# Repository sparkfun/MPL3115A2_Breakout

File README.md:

SparkFun MPL3115A2 Altitude/Pressure Sensor Breakout
====================================================

[  
*MPL3115A2 Altitude/Pressure Sensor Breakout (SEN-11084)*](https://www.sparkfun.com/products/11084)

The MPL3115A2 is a MEMS pressure sensor that provides Altitude data to within 30cm (with oversampling enabled). The sensor outputs are digitized by a high resolution 24-bit ADC and transmitted over I2C, meaning it's easy to interface with most controllers.

Repository Contents
-------------------
* **/Firmware** - Example Arduino sketch to use with the sensor.
* **/Hardware** - All Eagle design files (.brd, .sch)
* **/Libraries** - All Arduino libraries

Documentation
--------------
* **[Library](https://github.com/sparkfun/SparkFun_MPL3115A2_Breakout_Arduino_Library)** - Arduino library for the MPL3115A2.
* **[Hookup Guide](https://learn.sparkfun.com/tutorials/mpl3115a2-pressure-sensor-hookup-guide)** - Basic hookup guide for the MPL3115A2 Breakout.
* **[SparkFun Fritzing repo](https://github.com/sparkfun/Fritzing_Parts)** - Fritzing diagrams for SparkFun products.
* **[SparkFun 3D Model repo](https://github.com/sparkfun/3D_Models)** - 3D models of SparkFun products. 

License Information
-------------------
The hardware is released under [Creative Commons ShareAlike 4.0 International](https://creativecommons.org/licenses/by-sa/4.0/).
The code is beerware; if you see me (or any other SparkFun employee) at the local, and you've found our code helpful, please buy us a round!

Distributed as-is; no warranty is given.

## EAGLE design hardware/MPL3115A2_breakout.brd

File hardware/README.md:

# What Are these Files?

The .sch and .brd files hare are Eagle CAD schematic and PCB design files for the MPL3115A2 Breakout.

These files were created with Eagle 6.2.0. There is a free, lite, version of Eagle available from [cadsoftusa.com](cadsoftusa.com).

[Creative Commons Attribution-ShareAlike](http://creativecommons.org/licenses/by-sa/3.0/)

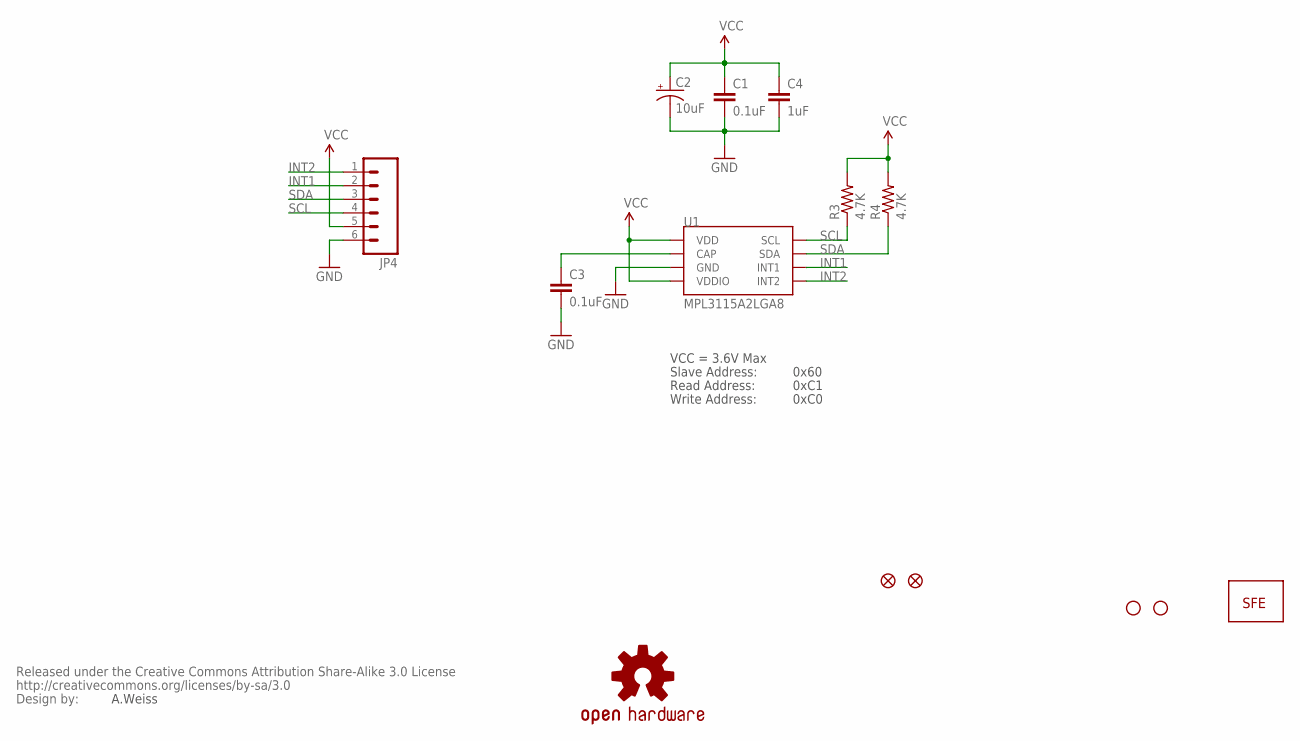
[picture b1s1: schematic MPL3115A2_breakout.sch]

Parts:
C1, C3: 0.1uF; 0603-CAP
C2: 10uF; EIA3216
C4: 1uF; 0603-CAP
JP1: LOGO-SFESK; SFE-LOGO-FLAME
JP2, JP3: STAND-OFF
JP4: M06SIP; 1X06
JP6, JP7: FIDUCIALUFIDUCIAL; MICRO-FIDUCIAL
R3, R4: 4.7K; 0603-RES
U1: MPL3115A2LGA8; LGA8
U$1: OSHW-LOGOS; OSHW-LOGO-S
U$2: CREATIVE_COMMONS

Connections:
GND: C1.2, C2.C (-), C3.2, C4.2, JP4.6, U1.3 (GND)
INT1: JP4.2, U1.6 (INT1)
INT2: JP4.1, U1.5 (INT2)
unnamed: C3.1, U1.2 (CAP)
SCL: JP4.4, R3.1, U1.8 (SCL)
SDA: JP4.3, R4.1, U1.7 (SDA)
VCC: C1.1, C2.A (+), C4.1, JP4.5, R3.2, R4.2, U1.1 (VDD), U1.4 (VDDIO)

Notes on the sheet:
A.Weiss
VCC = 3.6V Max
Read Address:
Write Address:
Slave Address:
0x60
0xC1
0xC0

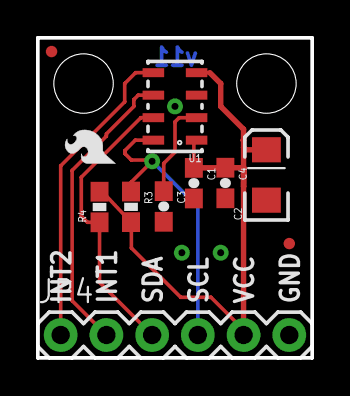
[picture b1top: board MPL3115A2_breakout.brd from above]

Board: 2 copper layers, 15.2 x 17.8 mm, 15 parts (1 on the bottom side), 7 nets.

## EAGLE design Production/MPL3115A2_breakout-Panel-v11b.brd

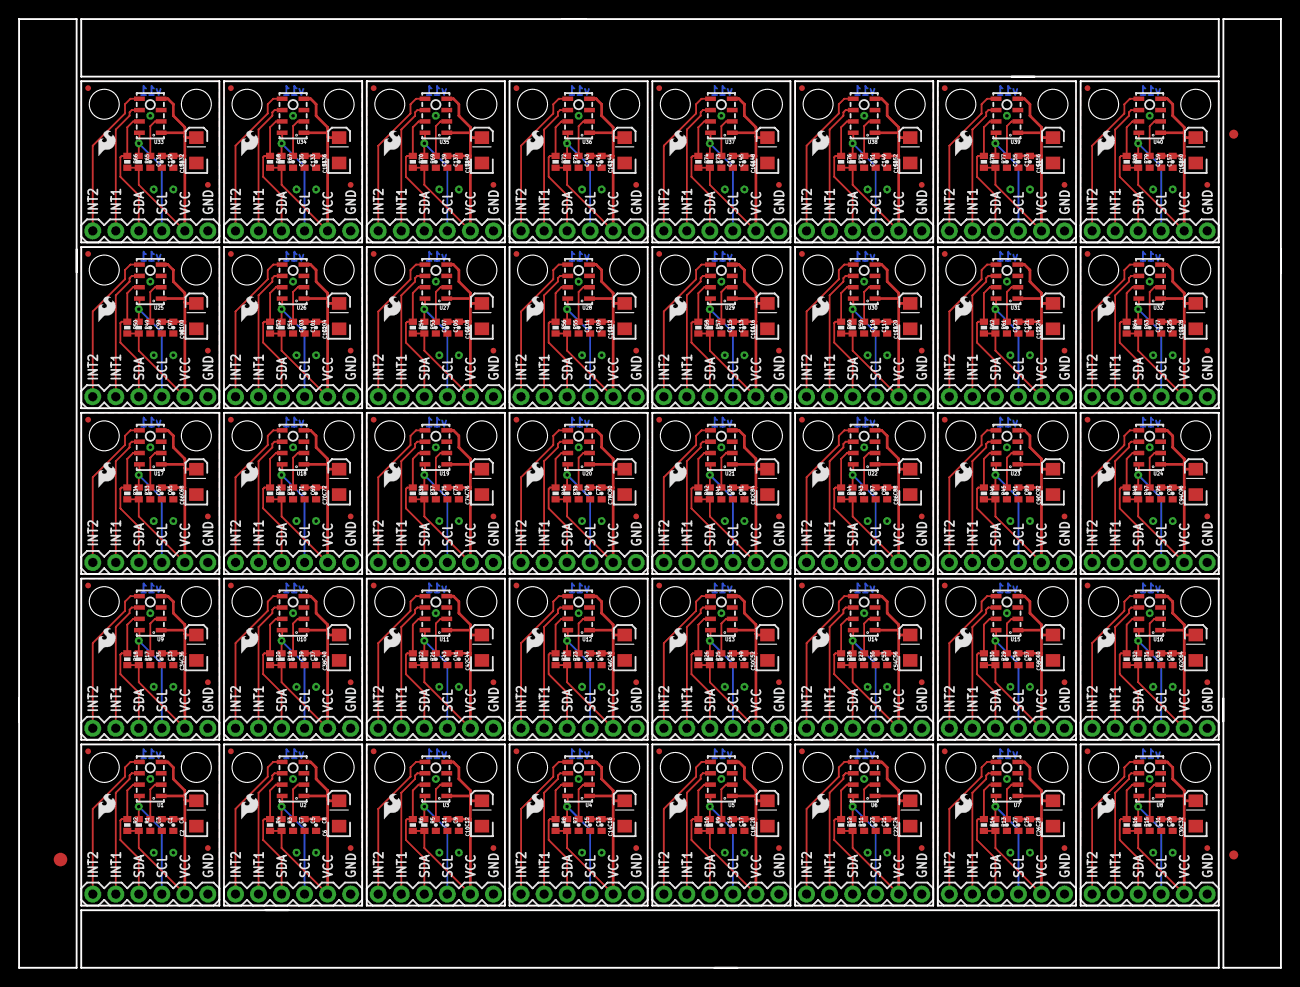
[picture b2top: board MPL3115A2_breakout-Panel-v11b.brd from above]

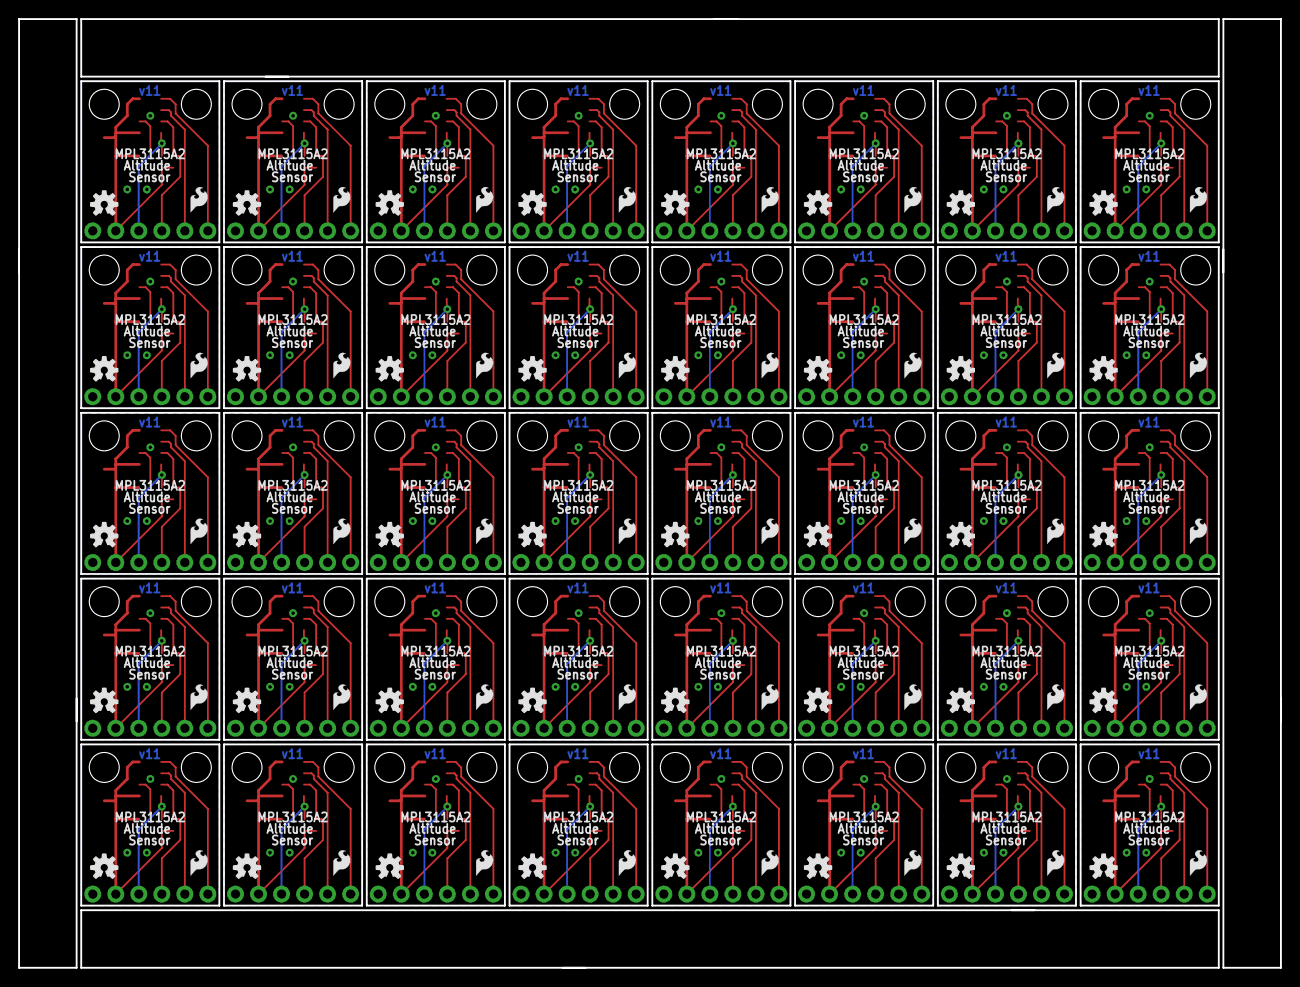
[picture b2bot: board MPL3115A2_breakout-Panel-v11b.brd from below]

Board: 2 copper layers, 139.2 x 104.6 mm, 603 parts (80 on the bottom side), 280 nets.

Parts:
C1, C3, C5, C7, C9, C11, C13, C15, C17, C19, C21, C23, C25, C27, C29, C31, C33, C35, C37, C39, C41, C43, C45, C47, C49, C51, C53, C55, C57, C59, C61, C63, C65, C67, C69, C71, C73, C75, C77, C79, C81, C83, C85, C87, C89, C91, C93, C95, C97, C99, C101, C103, C105, C107, C109, C111, C113, C115, C117, C119, C121, C123, C125, C127, C129, C131, C133, C135, C137, C139, C141, C143, C145, C147, C149, C151, C153, C155, C157, C159: 0.1uF; 0402-CAP
C2, C6, C10, C14, C18, C22, C26, C30, C34, C38, C42, C46, C50, C54, C58, C62, C66, C70, C74, C78, C82, C86, C90, C94, C98, C102, C106, C110, C114, C118, C122, C126, C130, C134, C138, C142, C146, C150, C154, C158: 10uF; EIA3216
C4, C8, C12, C16, C20, C24, C28, C32, C36, C40, C44, C48, C52, C56, C60, C64, C68, C72, C76, C80, C84, C88, C92, C96, C100, C104, C108, C112, C116, C120, C124, C128, C132, C136, C140, C144, C148, C152, C156, C160: 1uF; 0402-CAP
E$1: FIDUCIAL-1.5X3
E$5, E$6: FIDUCIAL-1X2
JP1, JP5, JP8, JP12, JP15, JP19, JP22, JP26, JP29, JP33, JP36, JP40, JP43, JP47, JP50, JP54, JP57, JP61, JP64, JP68, JP71, JP75, JP78, JP82, JP85, JP89, JP92, JP96, JP99, JP103, JP106, JP110, JP113, JP117, JP120, JP124, JP127, JP131, JP134, JP138, JP141, JP145, JP148, JP152, JP155, JP159, JP162, JP166, JP169, JP173, JP176, JP180, JP183, JP187, JP190, JP194, JP197, JP201, JP204, JP208, JP211, JP215, JP218, JP222, JP225, JP229, JP232, JP236, JP239, JP243, JP246, JP250, JP253, JP257, JP260, JP264, JP267, JP271, JP274, JP278: LOGO-SFESK; SFE-LOGO-FLAME
JP2, JP3, JP9, JP10, JP16, JP17, JP23, JP24, JP30, JP31, JP37, JP38, JP44, JP45, JP51, JP52, JP58, JP59, JP65, JP66, JP72, JP73, JP79, JP80, JP86, JP87, JP93, JP94, JP100, JP101, JP107, JP108, JP114, JP115, JP121, JP122, JP128, JP129, JP135, JP136, JP142, JP143, JP149, JP150, JP156, JP157, JP163, JP164, JP170, JP171, JP177, JP178, JP184, JP185, JP191, JP192, JP198, JP199, JP205, JP206, JP212, JP213, JP219, JP220, JP226, JP227, JP233, JP234, JP240, JP241, JP247, JP248, JP254, JP255, JP261, JP262, JP268, JP269, JP275, JP276: STAND-OFF
JP4, JP11, JP18, JP25, JP32, JP39, JP46, JP53, JP60, JP67, JP74, JP81, JP88, JP95, JP102, JP109, JP116, JP123, JP130, JP137, JP144, JP151, JP158, JP165, JP172, JP179, JP186, JP193, JP200, JP207, JP214, JP221, JP228, JP235, JP242, JP249, JP256, JP263, JP270, JP277: 1X06
JP6, JP7, JP13, JP14, JP20, JP21, JP27, JP28, JP34, JP35, JP41, JP42, JP48, JP49, JP55, JP56, JP62, JP63, JP69, JP70, JP76, JP77, JP83, JP84, JP90, JP91, JP97, JP98, JP104, JP105, JP111, JP112, JP118, JP119, JP125, JP126, JP132, JP133, JP139, JP140, JP146, JP147, JP153, JP154, JP160, JP161, JP167, JP168, JP174, JP175, JP181, JP182, JP188, JP189, JP195, JP196, JP202, JP203, JP209, JP210, JP216, JP217, JP223, JP224, JP230, JP231, JP237, JP238, JP244, JP245, JP251, JP252, JP258, JP259, JP265, JP266, JP272, JP273, JP279, JP280: FIDUCIALUFIDUCIAL; MICRO-FIDUCIAL
R1, R2, R3, R4, R5, R6, R7, R8, R9, R10, R11, R12, R13, R14, R15, R16, R17, R18, R19, R20, R21, R22, R23, R24, R25, R26, R27, R28, R29, R30, R31, R32, R33, R34, R35, R36, R37, R38, R39, R40, R41, R42, R43, R44, R45, R46, R47, R48, R49, R50, R51, R52, R53, R54, R55, R56, R57, R58, R59, R60, R61, R62, R63, R64, R65, R66, R67, R68, R69, R70, R71, R72, R73, R74, R75, R76, R77, R78, R79, R80: 1k; 0402-RES
U1, U2, U3, U4, U5, U6, U7, U8, U9, U10, U11, U12, U13, U14, U15, U16, U17, U18, U19, U20, U21, U22, U23, U24, U25, U26, U27, U28, U29, U30, U31, U32, U33, U34, U35, U36, U37, U38, U39, U40: MPL3115A2LGA8; LGA8
U$1, U$2, U$3, U$4, U$5, U$6, U$7, U$8, U$9, U$10, U$11, U$12, U$13, U$14, U$15, U$16, U$17, U$18, U$19, U$20, U$21, U$22, U$23, U$24, U$25, U$26, U$27, U$28, U$29, U$30, U$31, U$32, U$33, U$34, U$35, U$36, U$37, U$38, U$39, U$40: OSHW-LOGOS; OSHW-LOGO-S

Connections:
GND: C1.2, C2.C, C3.2, C4.2, JP4.6, U1.3
GND1: C5.2, C6.C, C7.2, C8.2, JP11.6, U2.3
GND2: C9.2, C10.C, C11.2, C12.2, JP18.6, U3.3
GND3: C13.2, C14.C, C15.2, C16.2, JP25.6, U4.3
GND4: C17.2, C18.C, C19.2, C20.2, JP32.6, U5.3
GND5: C21.2, C22.C, C23.2, C24.2, JP39.6, U6.3
GND6: C25.2, C26.C, C27.2, C28.2, JP46.6, U7.3
GND7: C29.2, C30.C, C31.2, C32.2, JP53.6, U8.3
GND8: C33.2, C34.C, C35.2, C36.2, JP60.6, U9.3
GND9: C37.2, C38.C, C39.2, C40.2, JP67.6, U10.3
GND10: C41.2, C42.C, C43.2, C44.2, JP74.6, U11.3
GND11: C45.2, C46.C, C47.2, C48.2, JP81.6, U12.3
GND12: C49.2, C50.C, C51.2, C52.2, JP88.6, U13.3
GND13: C53.2, C54.C, C55.2, C56.2, JP95.6, U14.3
GND14: C57.2, C58.C, C59.2, C60.2, JP102.6, U15.3
GND15: C61.2, C62.C, C63.2, C64.2, JP109.6, U16.3
GND16: C65.2, C66.C, C67.2, C68.2, JP116.6, U17.3
GND17: C69.2, C70.C, C71.2, C72.2, JP123.6, U18.3
GND18: C73.2, C74.C, C75.2, C76.2, JP130.6, U19.3
GND19: C77.2, C78.C, C79.2, C80.2, JP137.6, U20.3
GND20: C81.2, C82.C, C83.2, C84.2, JP144.6, U21.3
GND21: C85.2, C86.C, C87.2, C88.2, JP151.6, U22.3
GND22: C89.2, C90.C, C91.2, C92.2, JP158.6, U23.3
GND23: C93.2, C94.C, C95.2, C96.2, JP165.6, U24.3
GND24: C97.2, C98.C, C99.2, C100.2, JP172.6, U25.3
GND25: C101.2, C102.C, C103.2, C104.2, JP179.6, U26.3
GND26: C105.2, C106.C, C107.2, C108.2, JP186.6, U27.3
GND27: C109.2, C110.C, C111.2, C112.2, JP193.6, U28.3
GND28: C113.2, C114.C, C115.2, C116.2, JP200.6, U29.3
GND29: C117.2, C118.C, C119.2, C120.2, JP207.6, U30.3
GND30: C121.2, C122.C, C123.2, C124.2, JP214.6, U31.3
GND31: C125.2, C126.C, C127.2, C128.2, JP221.6, U32.3
GND32: C129.2, C130.C, C131.2, C132.2, JP228.6, U33.3
GND33: C133.2, C134.C, C135.2, C136.2, JP235.6, U34.3
GND34: C137.2, C138.C, C139.2, C140.2, JP242.6, U35.3
GND35: C141.2, C142.C, C143.2, C144.2, JP249.6, U36.3
GND36: C145.2, C146.C, C147.2, C148.2, JP256.6, U37.3
GND37: C149.2, C150.C, C151.2, C152.2, JP263.6, U38.3
GND38: C153.2, C154.C, C155.2, C156.2, JP270.6, U39.3
GND39: C157.2, C158.C, C159.2, C160.2, JP277.6, U40.3
INT1: JP4.2, U1.6
INT2: JP4.1, U1.5
INT3: JP11.2, U2.6
INT4: JP11.1, U2.5
INT5: JP18.2, U3.6
INT6: JP18.1, U3.5
INT7: JP25.2, U4.6
INT8: JP25.1, U4.5
INT9: JP32.2, U5.6
INT10: JP32.1, U5.5
INT11: JP39.2, U6.6
INT12: JP39.1, U6.5
INT13: JP46.2, U7.6
INT14: JP46.1, U7.5
INT15: JP53.2, U8.6
INT16: JP53.1, U8.5
INT17: JP60.2, U9.6
INT18: JP60.1, U9.5
INT19: JP67.2, U10.6
INT20: JP67.1, U10.5
INT21: JP74.2, U11.6
INT22: JP74.1, U11.5
INT23: JP81.2, U12.6
INT24: JP81.1, U12.5
INT25: JP88.2, U13.6
INT26: JP88.1, U13.5
INT27: JP95.2, U14.6
INT28: JP95.1, U14.5
INT29: JP102.2, U15.6
INT30: JP102.1, U15.5
INT31: JP109.2, U16.6
INT32: JP109.1, U16.5
INT33: JP116.2, U17.6
INT34: JP116.1, U17.5
INT35: JP123.2, U18.6
INT36: JP123.1, U18.5
INT37: JP130.2, U19.6
INT38: JP130.1, U19.5
INT39: JP137.2, U20.6
INT40: JP137.1, U20.5
INT41: JP144.2, U21.6
INT42: JP144.1, U21.5
INT43: JP151.2, U22.6
INT44: JP151.1, U22.5
INT45: JP158.2, U23.6
INT46: JP158.1, U23.5
INT47: JP165.2, U24.6
INT48: JP165.1, U24.5
INT49: JP172.2, U25.6
INT50: JP172.1, U25.5
INT51: JP179.2, U26.6
INT52: JP179.1, U26.5
INT53: JP186.2, U27.6
INT54: JP186.1, U27.5
INT55: JP193.2, U28.6
INT56: JP193.1, U28.5
INT57: JP200.2, U29.6
INT58: JP200.1, U29.5
INT59: JP207.2, U30.6
INT60: JP207.1, U30.5
INT61: JP214.2, U31.6
INT62: JP214.1, U31.5
INT63: JP221.2, U32.6
INT64: JP221.1, U32.5
INT65: JP228.2, U33.6
INT66: JP228.1, U33.5
INT67: JP235.2, U34.6
INT68: JP235.1, U34.5
INT69: JP242.2, U35.6
INT70: JP242.1, U35.5
INT71: JP249.2, U36.6
INT72: JP249.1, U36.5
INT73: JP256.2, U37.6
INT74: JP256.1, U37.5
INT75: JP263.2, U38.6
INT76: JP263.1, U38.5
INT77: JP270.2, U39.6
INT78: JP270.1, U39.5
INT79: JP277.2, U40.6
INT80: JP277.1, U40.5
unnamed: C7.1, U2.2
unnamed: C11.1, U3.2
unnamed: C3.1, U1.2
unnamed: C15.1, U4.2
unnamed: C19.1, U5.2
unnamed: C23.1, U6.2
unnamed: C27.1, U7.2
unnamed: C31.1, U8.2
unnamed: C35.1, U9.2
unnamed: C39.1, U10.2
unnamed: C43.1, U11.2
unnamed: C47.1, U12.2
unnamed: C51.1, U13.2
unnamed: C55.1, U14.2
unnamed: C59.1, U15.2
unnamed: C63.1, U16.2
unnamed: C67.1, U17.2
unnamed: C71.1, U18.2
unnamed: C75.1, U19.2
unnamed: C79.1, U20.2
unnamed: C83.1, U21.2
unnamed: C87.1, U22.2
unnamed: C91.1, U23.2
unnamed: C95.1, U24.2
unnamed: C99.1, U25.2
unnamed: C103.1, U26.2
unnamed: C107.1, U27.2
unnamed: C111.1, U28.2
unnamed: C115.1, U29.2
unnamed: C119.1, U30.2
unnamed: C123.1, U31.2
unnamed: C127.1, U32.2
unnamed: C131.1, U33.2
unnamed: C135.1, U34.2
unnamed: C139.1, U35.2
unnamed: C143.1, U36.2
unnamed: C147.1, U37.2
unnamed: C151.1, U38.2
unnamed: C155.1, U39.2
unnamed: C159.1, U40.2
SCL: JP4.4, R1.1, U1.8
SCL1: JP11.4, R3.1, U2.8
SCL2: JP18.4, R5.1, U3.8
SCL3: JP25.4, R7.1, U4.8
SCL4: JP32.4, R9.1, U5.8
SCL5: JP39.4, R11.1, U6.8
SCL6: JP46.4, R13.1, U7.8
SCL7: JP53.4, R15.1, U8.8
SCL8: JP60.4, R17.1, U9.8
SCL9: JP67.4, R19.1, U10.8
SCL10: JP74.4, R21.1, U11.8
SCL11: JP81.4, R23.1, U12.8
SCL12: JP88.4, R25.1, U13.8
SCL13: JP95.4, R27.1, U14.8
SCL14: JP102.4, R29.1, U15.8
SCL15: JP109.4, R31.1, U16.8
SCL16: JP116.4, R33.1, U17.8
SCL17: JP123.4, R35.1, U18.8
SCL18: JP130.4, R37.1, U19.8
SCL19: JP137.4, R39.1, U20.8
SCL20: JP144.4, R41.1, U21.8
SCL21: JP151.4, R43.1, U22.8
SCL22: JP158.4, R45.1, U23.8
SCL23: JP165.4, R47.1, U24.8
SCL24: JP172.4, R49.1, U25.8
SCL25: JP179.4, R51.1, U26.8
SCL26: JP186.4, R53.1, U27.8
SCL27: JP193.4, R55.1, U28.8
SCL28: JP200.4, R57.1, U29.8
SCL29: JP207.4, R59.1, U30.8
SCL30: JP214.4, R61.1, U31.8
SCL31: JP221.4, R63.1, U32.8
SCL32: JP228.4, R65.1, U33.8
SCL33: JP235.4, R67.1, U34.8
SCL34: JP242.4, R69.1, U35.8
SCL35: JP249.4, R71.1, U36.8
SCL36: JP256.4, R73.1, U37.8
SCL37: JP263.4, R75.1, U38.8
SCL38: JP270.4, R77.1, U39.8
SCL39: JP277.4, R79.1, U40.8
SDA: JP4.3, R2.1, U1.7
SDA1: JP11.3, R4.1, U2.7
SDA2: JP18.3, R6.1, U3.7
SDA3: JP25.3, R8.1, U4.7
SDA4: JP32.3, R10.1, U5.7
SDA5: JP39.3, R12.1, U6.7
SDA6: JP46.3, R14.1, U7.7
SDA7: JP53.3, R16.1, U8.7
SDA8: JP60.3, R18.1, U9.7
SDA9: JP67.3, R20.1, U10.7
SDA10: JP74.3, R22.1, U11.7
SDA11: JP81.3, R24.1, U12.7
SDA12: JP88.3, R26.1, U13.7
SDA13: JP95.3, R28.1, U14.7
SDA14: JP102.3, R30.1, U15.7
SDA15: JP109.3, R32.1, U16.7
SDA16: JP116.3, R34.1, U17.7
SDA17: JP123.3, R36.1, U18.7
SDA18: JP130.3, R38.1, U19.7
SDA19: JP137.3, R40.1, U20.7
SDA20: JP144.3, R42.1, U21.7
SDA21: JP151.3, R44.1, U22.7
SDA22: JP158.3, R46.1, U23.7
SDA23: JP165.3, R48.1, U24.7
SDA24: JP172.3, R50.1, U25.7
SDA25: JP179.3, R52.1, U26.7
SDA26: JP186.3, R54.1, U27.7
SDA27: JP193.3, R56.1, U28.7
SDA28: JP200.3, R58.1, U29.7
SDA29: JP207.3, R60.1, U30.7
SDA30: JP214.3, R62.1, U31.7
SDA31: JP221.3, R64.1, U32.7
SDA32: JP228.3, R66.1, U33.7
SDA33: JP235.3, R68.1, U34.7
SDA34: JP242.3, R70.1, U35.7
SDA35: JP249.3, R72.1, U36.7
SDA36: JP256.3, R74.1, U37.7
SDA37: JP263.3, R76.1, U38.7
SDA38: JP270.3, R78.1, U39.7
SDA39: JP277.3, R80.1, U40.7
VCC: C1.1, C2.A, C4.1, JP4.5, R1.2, R2.2, U1.1, U1.4
VCC1: C5.1, C6.A, C8.1, JP11.5, R3.2, R4.2, U2.1, U2.4
VCC2: C9.1, C10.A, C12.1, JP18.5, R5.2, R6.2, U3.1, U3.4
VCC3: C13.1, C14.A, C16.1, JP25.5, R7.2, R8.2, U4.1, U4.4
VCC4: C17.1, C18.A, C20.1, JP32.5, R9.2, R10.2, U5.1, U5.4
VCC5: C21.1, C22.A, C24.1, JP39.5, R11.2, R12.2, U6.1, U6.4
VCC6: C25.1, C26.A, C28.1, JP46.5, R13.2, R14.2, U7.1, U7.4
VCC7: C29.1, C30.A, C32.1, JP53.5, R15.2, R16.2, U8.1, U8.4
VCC8: C33.1, C34.A, C36.1, JP60.5, R17.2, R18.2, U9.1, U9.4
VCC9: C37.1, C38.A, C40.1, JP67.5, R19.2, R20.2, U10.1, U10.4
VCC10: C41.1, C42.A, C44.1, JP74.5, R21.2, R22.2, U11.1, U11.4
VCC11: C45.1, C46.A, C48.1, JP81.5, R23.2, R24.2, U12.1, U12.4
VCC12: C49.1, C50.A, C52.1, JP88.5, R25.2, R26.2, U13.1, U13.4
VCC13: C53.1, C54.A, C56.1, JP95.5, R27.2, R28.2, U14.1, U14.4
VCC14: C57.1, C58.A, C60.1, JP102.5, R29.2, R30.2, U15.1, U15.4
VCC15: C61.1, C62.A, C64.1, JP109.5, R31.2, R32.2, U16.1, U16.4
VCC16: C65.1, C66.A, C68.1, JP116.5, R33.2, R34.2, U17.1, U17.4
VCC17: C69.1, C70.A, C72.1, JP123.5, R35.2, R36.2, U18.1, U18.4
VCC18: C73.1, C74.A, C76.1, JP130.5, R37.2, R38.2, U19.1, U19.4
VCC19: C77.1, C78.A, C80.1, JP137.5, R39.2, R40.2, U20.1, U20.4
VCC20: C81.1, C82.A, C84.1, JP144.5, R41.2, R42.2, U21.1, U21.4
VCC21: C85.1, C86.A, C88.1, JP151.5, R43.2, R44.2, U22.1, U22.4
VCC22: C89.1, C90.A, C92.1, JP158.5, R45.2, R46.2, U23.1, U23.4
VCC23: C93.1, C94.A, C96.1, JP165.5, R47.2, R48.2, U24.1, U24.4
VCC24: C97.1, C98.A, C100.1, JP172.5, R49.2, R50.2, U25.1, U25.4
VCC25: C101.1, C102.A, C104.1, JP179.5, R51.2, R52.2, U26.1, U26.4
VCC26: C105.1, C106.A, C108.1, JP186.5, R53.2, R54.2, U27.1, U27.4
VCC27: C109.1, C110.A, C112.1, JP193.5, R55.2, R56.2, U28.1, U28.4
VCC28: C113.1, C114.A, C116.1, JP200.5, R57.2, R58.2, U29.1, U29.4
VCC29: C117.1, C118.A, C120.1, JP207.5, R59.2, R60.2, U30.1, U30.4
VCC30: C121.1, C122.A, C124.1, JP214.5, R61.2, R62.2, U31.1, U31.4
VCC31: C125.1, C126.A, C128.1, JP221.5, R63.2, R64.2, U32.1, U32.4
VCC32: C129.1, C130.A, C132.1, JP228.5, R65.2, R66.2, U33.1, U33.4
VCC33: C133.1, C134.A, C136.1, JP235.5, R67.2, R68.2, U34.1, U34.4
VCC34: C137.1, C138.A, C140.1, JP242.5, R69.2, R70.2, U35.1, U35.4
VCC35: C141.1, C142.A, C144.1, JP249.5, R71.2, R72.2, U36.1, U36.4
VCC36: C145.1, C146.A, C148.1, JP256.5, R73.2, R74.2, U37.1, U37.4
VCC37: C149.1, C150.A, C152.1, JP263.5, R75.2, R76.2, U38.1, U38.4
VCC38: C153.1, C154.A, C156.1, JP270.5, R77.2, R78.2, U39.1, U39.4
VCC39: C157.1, C158.A, C160.1, JP277.5, R79.2, R80.2, U40.1, U40.4

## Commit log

2013-01-04 first
    v11 hardware
2013-01-04 added firmware
    v10 firmware
2013-01-04 changed firmware file name
2013-01-15 merged ino files into one
2013-03-08 superficial readme cleanup
2013-04-22 Update README files.
2013-09-25 Large update. Faster, more accurate measurements.
    Found an error - example code was incorrectly preloading the BAR_IN
    registers (not needed). Fixed lots of polling issues. Removed hard coded
    register reads and hex writes. A lot more portable now.
2013-09-25 Initial commit of library.
    Works well. Needs some clean up.
2013-09-25 Removing original ino.
2013-09-25 Adding new example sketch.
2013-09-25 Corrected examples directory structure. Added more examples.
2013-09-25 Correct small error in example sketches.
2013-09-30 Adding available function names to example sketches.
2013-10-06 Added example to display "altimeter setting" Inches Mercury.
    This example coverts pressure from Pascals to inches of mercury,
    altimeter setting adjusted. This type of pressure reading is used in the
    USA on Wunderground. I find it SUPER weird, but it is needed for home
    weather stations and aircraft.
2013-10-08 Update MPL3115A2.ino
    For projects that require instantaneous read limited only by the sensor's OverSampleRate, you must set FIFO mode (in the F_SETUP register) to non-zero and toggle the OST bit (in the CTRL_REG1 registe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
    Changes were made in the main read() functions as well, as the break loop didn't break out of anything -- the code below it was still running even when no new data was available for acquisition.
2013-10-21 Creating zip of library for tutorial linking.
2013-10-22 Working out some bugs using one shot.
    The basic example doesn't quite work but this is a large improvement
    over previous code. User jr4284 pointed out some really novice bugs.
    Thanks jr2482!
2013-10-23 Changed sensor checking to one shot polling.
    The readPressure, readAltitude, and readTemp now check the PDR/TDR bits
    along with an OST toggle for as fast as possible data sampling. It could
    go faster if we read pressure and temp at same time.
2013-12-04 Adding fritzing part
2014-01-07 Fixed negative temp bug reported by D.D.G.
    See comment:
    https://www.sparkfun.com/products/12081#comment-52ca1b6dce395f75238b4569
2014-02-16 Create FIFOExample
2014-02-16 Update FIFOExample
2014-02-16 Add MPL3115A2 FIFO example
2014-02-17 FIFO example for the MPL3115A2
    Added autonomous logging capability using the internal 32-sample FIFO
    data storage. This example displays information about the sensor status
    to an LCD. The microcontroller is a 3.3 V Pro Mini.
2014-02-17 Update MPL3115A2_AdvancedExample
2014-02-18 Update MPL3115A2_AdvancedExample.ino
    Corrected some typos...
2014-02-18 Update MPL3115A2_AdvancedExample.ino
    Corrected more typos...
2014-02-19 Added unsigned long data type to FIFO data interval
    The time between FIFO data reads can get quite long; I had to designate
    the data types of the corresponding indices as unsigned long to get the
    proper response. Still, I get a spuriously large number when using the
    largest time interval. Am I trying to use a number too big for this
    processor?
2014-03-11 Fix problems with not using Wire
    As seen on pylon's posts here: http://forum.arduino.cc/index.php?topic=224241.0
2014-08-20 Cleared compiler warnings - begin() does not return a value -- changed the return type to "void" - used binary constant from Arduino's binary.h, instead of relying on gcc compiler
2014-10-16 Added barometer calibration functions
    Added barometer calibration functions to obtain more precise altitude
    measurements (and barometer readouts)
2014-12-12 add missing parenthesis
    Equals comparison has higher precedence than bitwise &, so toggleOneShot() wasn't happening for the first temperature reading if not preceded by another read function with a call to toggleOneShot().
    Also make readAltitude() consistent with other read functions and fix some indentation.
2015-01-14 Computer change
2015-02-03 Adding Simple Sketch
2015-04-24 Squashed 'Libraries/Arduino/' content from commit dc8bee5
    git-subtree-dir: Libraries/Arduino
    git-subtree-split: dc8bee53b4dc3c0b60c77df72f6b337520671fc1
2015-04-24 Incorporating Arduino library subtree, adding Library README
2015-04-30 Updating repo structure, adding links to hookup guide, fritzing repo to README
2015-04-30 Squashed 'Libraries/Arduino/' changes from dc8bee5..cfe5d42
    git-subtree-dir: Libraries/Arduino
    git-subtree-split: cfe5d42c5efc6b926fb8f38e7392a543fab7ad10
2015-07-07 Squashed 'Libraries/Arduino/' changes from cfe5d42..0fa3f67
    0fa3f67 Fixing library name to prevent compilation errors
    git-subtree-dir: Libraries/Arduino
    git-subtree-split: 0fa3f670825eb1eb5669f5fff5ad725046e93d3b
2015-08-04 Squashed 'Libraries/Arduino/' changes from 0fa3f67..4f35b5f
    4f35b5f Update SparkFunMPL3115A2.h
    git-subtree-dir: Libraries/Arduino
    git-subtree-split: 4f35b5f0f62d251939959802edecf62588d0115d
2016-05-23 created panel v11b
2025-06-27 Update README.md
    Updating link

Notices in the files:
parts and their libraries:
SparkFun-Sensors: Licensing: CC v3.0 Share-Alike You are welcome to use this library for commercial purposes.
SparkFun-Retired: Licensing:Creative Commons ShareAlike 4.0 International - https://creativecommons.org/licenses/by-sa/4.0
